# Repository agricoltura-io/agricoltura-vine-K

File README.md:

# agricoltura-vine-K
daisy chainable interface for relay control of high voltage devices for various agriculture applications, wired RS485 system, powered by 24VAC

Quick Specs:
- ST Microelectronics STM32F446RET6 ARM Cortex M4F 180MHZ MCU
- 5V Tolerant Analog Inputs
- 8x I2C interfaces
- 4x UART interface (via mux)
- 8x 5V digital IO ports
- 2x G5LE-14 DC5 SPDT Relays
- USB 2.0 connectivity
- RS485 port
- 24VAC power input
- 2A 3.3V DCDC Regulator, for supporting lots of sensors
- 2A 5V DCDC Regulator, for 5V IO and other devices

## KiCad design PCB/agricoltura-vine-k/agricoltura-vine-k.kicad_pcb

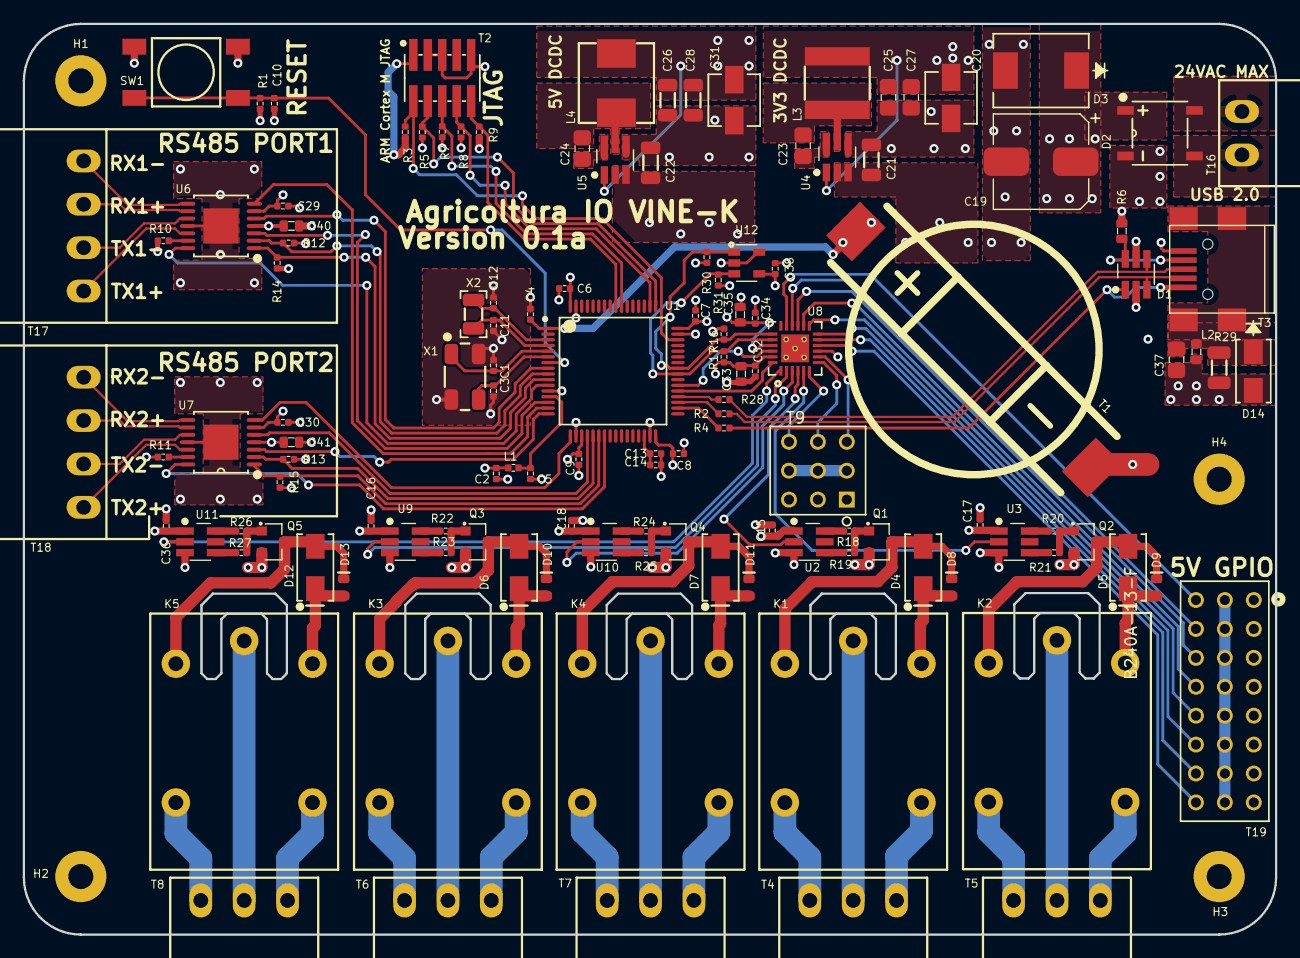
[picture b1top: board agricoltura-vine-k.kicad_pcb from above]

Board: 4 copper layers, 110.0 x 80.0 mm, 131 parts (0 on the bottom side), 109 nets.

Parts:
C1, C3: GCM1555C1H180GA16D; C0402
C2, C4, C5, C6, C7, C8, C9, C10, C13, C15, C16, C17, C18, C29, C30, C32, C34, C36, C38: C0402C104K9PACTU; R0402
C11, C12: CL05C090CB5NNNC; C0402
C14: GRM155R60J475ME47D; C0402
C19: UUQ1H470MCL1GS; CP_Elec_8x10
C20, C31: UCM1C470MCL1GS
C21, C22: GRT31CR61H106KE01L; C1206
C23: C0805C104M5RACTU; C0805
C24: C2012X7R2A104K125AA; C0805
C25, C27: GRM21BD70J226ME44L; C0805
C26, C28: GRT31CC81C226KE01L; C1206
C33, C35: GRM188R61A106KE69J; C0603
C37: C0805C103KCRACAUTO; C0805
C40, C41: CGA3E2X7R1H104K080AA; C0603
D1: ESDA6V1BC6; SOT-23-6_Handsoldering
D2: ABS210-13
D3: SMDJ15CA
D4, D5, D6, D7, D12: B240A-13-F
D8, D9, D10, D11, D13: LTST-C194TBKT; LED0603
D14: SMAJ30CA
H1, H2, H3, H4: M2_Plated_Hole; M2_HOLE
K1, K2, K3, K4, K5: G5LE-14_DC5
L1: BLM15HG601SN1D
L2: MI0603K300R-10
L3: ASPI-0628-3R9M-T1
L4: SRP6540-4R7M
Q1, Q2, Q3, Q4, Q5: IRLML6346TRPBF; SOT-23
R1, R3, R5, R7, R8, R9, R10, R11, R12, R13, R14, R15: RC0402FR-071KL; R0402
R2, R28: RC0402FR-0722RL; R0402
R4: RC0402FR-0710KL; R0402
R6: RC0603FR-0747KL; R0603
R16, R17, R30, R31: RC0402FR-074K7L; R0402
R18, R19, R20, R21, R22, R23, R24, R25, R26, R27: RC0402FR-0710RL; R0402
R29: RC1206FR-071ML; R1206
SW1: TL3301NF260QG
T1: BU2032SM-JJ-GTR
T2: 20021121-00010C4LF
T3: 0675031020; USB_Mini-B
T4, T5, T6, T7, T8: 0395121003
T9: TSW-103-07-G-T
T16: 0395121002
T17, T18: 0395121004
T19: TSW-108-07-G-T
U1: STM32F446RET6
U2, U3, U9, U10, U11: ZXGD3009E6TA; SOT-23-6_Handsoldering
U4: AP63203WU-7; SOT-23-6_Handsoldering
U5: AP63205WU-7; SOT-23-6_Handsoldering
U6, U7: MAX13450EAUD+; MAX13450EAUD&plus_
U8: TCA6416ARTWR
U12: AT24C16D-STUM-T; SOT-23-5
X1: ABM3B-8.000MHZ-B2-T; ABM3B8.000MHZB2T
X2: ABS07-32.768KHZ-9-T

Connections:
+3V3: C2.1, C6.1, C7.1, C8.1, C9.1, C20.1, C25.1, C27.1, C29.1, C30.1, C32.1, C33.1, C38.1, L1.1, L3.2, R1.1, R3.1, R5.1, R7.1, R8.1, R9.1, R12.1, R13.1, R14.1, R15.1, R16.1, R17.1, R30.1, R31.1, T2.1, U1.19, U1.32, U1.48, U1.64, U4.1, U6.6, U7.6, U8.23, U12.4
+5V: C15.2, C16.2, C17.2, C18.2, C26.1, C28.1, C31.1, C34.1, C35.1, C36.2, C40.1, C41.1, D4.2, D5.2, D6.2, D7.2, D8.1, D9.1, D10.1, D11.1, D12.2, D13.1, K1.2, K2.2, K3.2, K4.2, K5.2, L4.2, T9.2, T9.5, T9.8, T19.2, T19.5, T19.8, T19.11, T19.14, T19.17, T19.20, T19.23, U2.1, U3.1, U5.1, U6.4, U7.4, U8.21, U9.1, U10.1, U11.1
+24V: C19.1, C21.1, C22.1, D2.1, D3.1, U4.2, U4.3, U5.2, U5.3
/5V IO Interfaces/DRV1: U3.2, U8.5
/5V IO Interfaces/DRV2: U2.2, U8.4
/5V IO Interfaces/DRV3: U8.3, U10.2
/5V IO Interfaces/DRV4: U8.2, U9.2
/5V IO Interfaces/DRV5: U8.1, U11.2
/5V IO Interfaces/IO_INT_N: U1.38, U8.22
/5V IO Interfaces/IO_RESET: U1.37, U8.24
/5V IO Interfaces/IO_SCL: R16.2, R30.2, U1.41, U8.19, U12.1
/5V IO Interfaces/IO_SDA: R17.2, R31.2, U1.40, U8.20, U12.3
/Power Supply/24VAC+: D2.4, T16.1
/Power Supply/24VAC-: D2.2, T16.2
/RS485 Interface/RS485_DE1: R14.2, U1.10, U6.1
/RS485 Interface/RS485_DE2: R15.2, U1.22, U7.1
/RS485 Interface/RS485_RE1: R12.2, U1.9, U6.2
/RS485 Interface/RS485_RE2: R13.2, U1.21, U7.2
/RS485 Interface/RS485_RX1+: T17.2, U6.9
/RS485 Interface/RS485_RX1-: T17.1, U6.8
/RS485 Interface/RS485_RX2+: T18.2, U7.9
/RS485 Interface/RS485_RX2-: T18.1, U7.8
/RS485 Interface/RS485_SL_RATE1: U1.11, U6.14
/RS485 Interface/RS485_SL_RATE2: U1.23, U7.14
/RS485 Interface/RS485_TERM_EN1: U1.8, U6.5
/RS485 Interface/RS485_TERM_EN2: U1.20, U7.5
/RS485 Interface/RS485_TX1+: T17.4, U6.12
/RS485 Interface/RS485_TX1-: T17.3, U6.10
/RS485 Interface/RS485_TX2+: T18.4, U7.12
/RS485 Interface/RS485_TX2-: T18.3, U7.10
/RS485 Interface/RS485_UART_RX1: U1.15, U6.7
/RS485 Interface/RS485_UART_RX2: U1.17, U7.7
/RS485 Interface/RS485_UART_TX1: U1.14, U6.3
/RS485 Interface/RS485_UART_TX2: U1.16, U7.3
/STM32F446RET Controller/D+: D1.4, R28.2, T3.3
/STM32F446RET Controller/D-: D1.3, R2.2, T3.2
/STM32F446RET Controller/ID: D1.6, R6.1, T3.4
/STM32F446RET Controller/MCU_D+: R28.1, U1.36
/STM32F446RET Controller/MCU_D-: R2.1, U1.35
/STM32F446RET Controller/MCU_VBUS: R4.1, U1.34
/STM32F446RET Controller/NJTRST: R9.2, T2.10, U1.56
/STM32F446RET Controller/NRST: C10.1, R1.2, SW1.1, SW1.2, U1.7
/STM32F446RET Controller/OSC32_IN: C12.2, U1.3, X2.2
/STM32F446RET Controller/OSC32_OUT: U1.4, X2.1
/STM32F446RET Controller/OSC_IN: C1.1, U1.5, X1.1
/STM32F446RET Controller/OSC_OUT: C3.1, U1.6, X1.3
/STM32F446RET Controller/SWCLK_TCK: R5.2, T2.4, U1.49
/STM32F446RET Controller/SWDIO_TMS: R3.2, T2.2, U1.46
/STM32F446RET Controller/SWO_TDI: R8.2, T2.8, U1.50
/STM32F446RET Controller/SWO_TDO: R7.2, T2.6, U1.55
/STM32F446RET Controller/VBAT: C4.1, T1.1, U1.1
/STM32F446RET Controller/VBUS: D1.1, R4.2, T3.1
/STM32F446RET Controller/VCAP1: C13.1, C14.1, U1.30
/STM32F446RET Controller/VDDA: C5.1, L1.2, U1.13
Earth: H1.1, H2.1, H3.1, H4.1
GND: C1.2, C2.2, C3.2, C4.2, C5.2, C6.2, C7.2, C8.2, C9.2, C10.2, C11.1, C12.1, C13.2, C14.2, C15.1, C16.1, C17.1, C18.1, C19.2, C20.2, C21.2, C22.2, C25.2, C26.2, C27.2, C28.2, C29.2, C30.2, C31.2, C32.2, C33.2, C34.2, C35.2, C36.1, C37.2, C38.2, C40.2, C41.2, D1.2, D1.5, D2.3, D3.2, D14.2, L2.2, Q1.2, Q2.2, Q3.2, Q4.2, Q5.2, R6.2, R10.2, R11.2, R29.1, SW1.3, SW1.4, T1.2, T2.3, T2.5, T2.9, T3.5, T9.1, T9.4, T9.7, T19.1, T19.4, T19.7, T19.10, T19.13, T19.16, T19.19, T19.22, U1.12, U1.18, U1.31, U1.47, U1.63, U2.3, U3.3, U4.4, U5.4, U6.11, U6.15, U7.11, U7.15, U8.9, U8.25, U9.3, U10.3, U11.3, U12.2, U12.5, X1.2, X1.4
unnamed: C23.1, U4.6
unnamed: C23.2, L3.1, U4.5
unnamed: C24.1, U5.6
unnamed: C24.2, L4.1, U5.5
unnamed: C37.1, D14.1, L2.1, R29.2, T3.6
unnamed: D4.1, D8.2, K1.5, Q1.3
unnamed: D5.1, D9.2, K2.5, Q2.3
unnamed: D6.1, D10.2, K3.5, Q3.3
unnamed: D7.1, D11.2, K4.5, Q4.3
unnamed: D12.1, D13.2, K5.5, Q5.3
unnamed: K1.1, T4.2
unnamed: K1.3, T4.3
unnamed: K1.4, T4.1
unnamed: K2.1, T5.2
unnamed: K2.3, T5.3
unnamed: K2.4, T5.1
unnamed: K3.1, T6.2
unnamed: K3.3, T6.3
unnamed: K3.4, T6.1
unnamed: K4.1, T7.2
unnamed: K4.3, T7.3
unnamed: K4.4, T7.1
unnamed: K5.1, T8.2
unnamed: K5.3, T8.3
unnamed: K5.4, T8.1
unnamed: Q1.1, R18.2, R19.2
unnamed: Q2.1, R20.2, R21.2
unnamed: Q3.1, R22.2, R23.2
unnamed: Q4.1, R24.2, R25.2
unnamed: Q5.1, R26.2, R27.2
unnamed: R10.1, U6.13
unnamed: R11.1, U7.13
unnamed: R18.1, U2.6
unnamed: R19.1, U2.4
unnamed: R20.1, U3.6
unnamed: R21.1, U3.4
unnamed: R22.1, U9.6
unnamed: R23.1, U9.4
unnamed: R24.1, U10.6
unnamed: R25.1, U10.4
unnamed: R26.1, U11.6
unnamed: R27.1, U11.4
unnamed: T9.3, U8.8
unnamed: T9.6, U8.7
unnamed: T9.9, U8.6
unnamed: T19.3, U8.17
unnamed: T19.6, U8.16
unnamed: T19.9, U8.15
unnamed: T19.12, U8.14
unnamed: T19.15, U8.13
unnamed: T19.18, U8.12
unnamed: T19.21, U8.11
unnamed: T19.24, U8.10

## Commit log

2020-07-02 Project Created and Datasheets
    Project Created based on Vine project, added collection of datasheets.
2020-07-02 Relay and Board
    Relay circuits added and exported to PCB
2020-07-03 PCB Routing PRogress
    5th relay added to schematic, PCB section with Relays routed, still need to connecto IO expander channels.
2020-07-03 Finished
    PCB routing complete, up for review before fab.
2020-07-17 Boot Mode Guide
    guide for STM32 boot modes added
2020-07-24 EEPROM
    added EEPROM to IO expander serial port. Broke out remaining IO expander pins to header. Adjusted silkscreen labeling and reset button position to match the other Vine.
2021-02-08 PCB Tweaks
    PCB tweaked for packaging in water resistant housing for greenhouse deployment
2024-03-26 Create License.md
    added license
2024-03-26 kICAD 8
    Projected updated to KiCAD 8

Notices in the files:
parts and their libraries:
Copyright 2016 Accelerated Designs. All rights reserved.
